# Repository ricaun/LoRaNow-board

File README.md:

# LoRaNow Board

LoRaNow Boards is a project with open source hardware using the Arduino (atmega328p) and LoRa Module (RFM95).

This boards were designed to work with [LoRaNow Library][3].

## LoRaNow v0

## LoRaNow v1

## License

<br />This work is licensed under a <a rel="license" href="http://creativecommons.org/licenses/by-nc-sa/4.0/">Creative Commons Attribution-NonCommercial-ShareAlike 4.0 International License</a>.

If you want to do commercial stuff with this project, please contact [ricaun][1] so we can organize an simple agreement.

## Blog

See news and other projects on my [blog][2] 

[1]: http://www.ricaun.com.br/#contact
[2]: http://www.loranow.com
[3]: https://github.com/ricaun/LoRaNow

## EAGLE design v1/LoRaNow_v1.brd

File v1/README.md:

# LoRaNow v1

LoRaNow Boards v1 is a PCB to help wiring between Atmega328p and RFM95 LoRa module to work with 2 AA batteries.

## Detailed Description

This board has:
* Footprint for Atmega328p
* Footprint for RFM95
* Footprint for P-Channel Mosfet to turn on/off the RFM95
* Classic I2C connector (VCC, GND, SCL, SDA)
* Footprint for Diodes (DIO0/DIO1/DIO2 to pin 2)
* Footprint for Ultra Low Power controller TPL5110 (Optional)

Look at the schematics for more informations.

Pins board connections.
```
  Arduino       RFM9x Module
  13 <--------> CLK
  12 <--------> MISO
  11 <--------> MOSI
  10 <--------> CS
  9  <--------> P-MOSFET
  2  <-DIODES-> DIO0/DIO1/DIO2
```

## Schematic

## Boards

## Bill Of Material

* Atmega328p (SMD)
* 8MHz cystal (SMD)
* RFM95 (check Frequency)
* Resistor 10k (603) (x2)
* Capacitor 1u (603)
* Capacitor 0.1u (603) (x5)
* P-Channel Mosfet (SOT23)
* 1N4148 (SOD123) (x3)
* Ultra Low Power controller TPL5110
* Resistor 124k (603)
* Battery holder (2xAA)
* Antenna 

## License

<br />This work is licensed under a <a rel="license" href="http://creativecommons.org/licenses/by-nc-sa/4.0/">Creative Commons Attribution-NonCommercial-ShareAlike 4.0 International License</a>.

If you want to do commercial stuff with this project, please contact [ricaun][1] so we can organize an simple agreement.

## Blog

See news and other projects on my [blog][2] 

[1]: http://www.ricaun.com.br/#contact
[2]: http://www.loranow.com

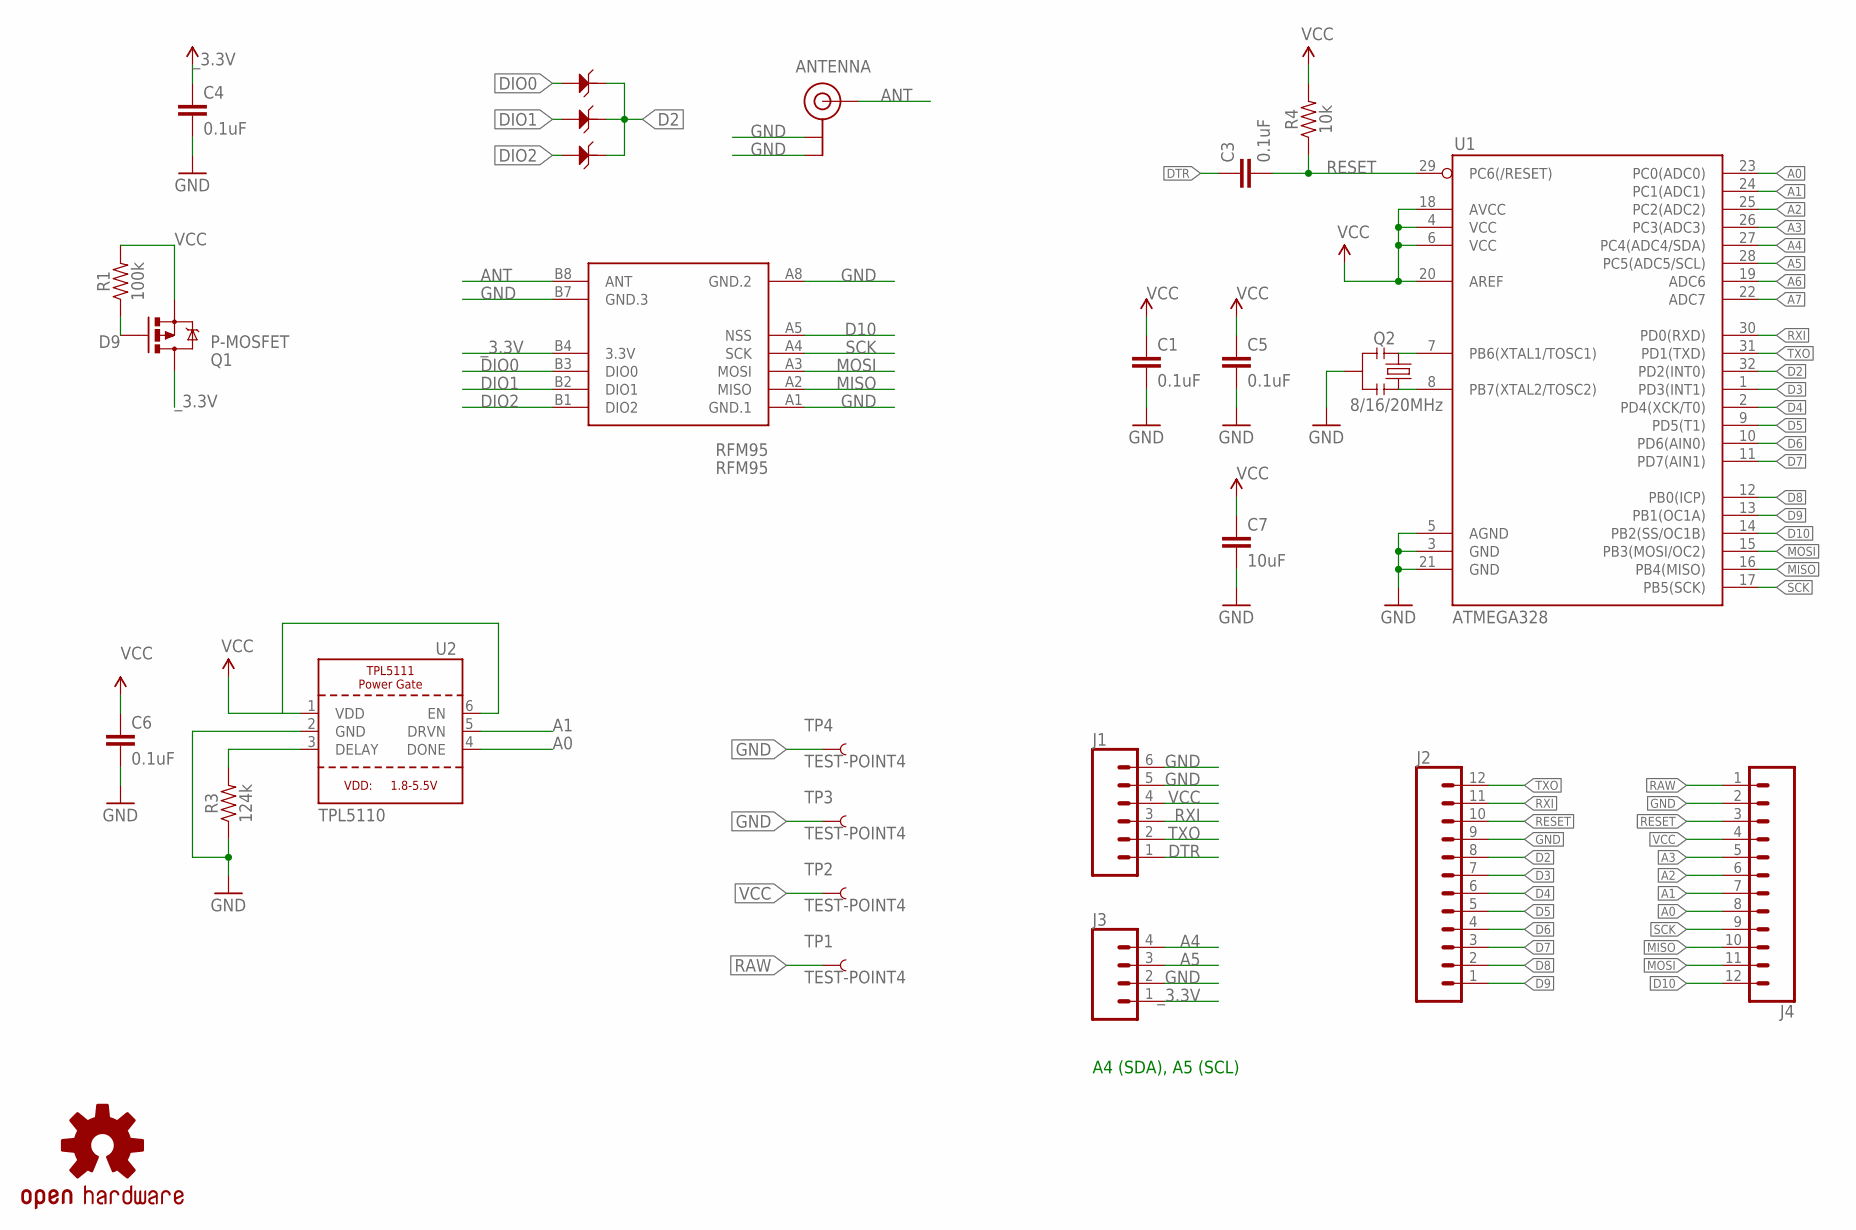
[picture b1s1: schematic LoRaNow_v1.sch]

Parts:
ANTENNA: U.FLU.FL_2A; U.FL_2A
C1, C3, C4, C5, C6: 0.1uF; 0603
C7: 10uF; 0603
D2, D3, D4: 1N4148; SOD123-2.7X1.6
J1: CONN_06NO_SILK_FEMALE_PTH; 1X06_NO_SILK
J2, J4: CONN_12NO_SILK; 1X12_NO_SILK
J3: CONN_041X04_NO_SILK; 1X04_NO_SILK
Q1: P-MOSFET; SOT23-3
Q2: 8/16/20MHz; RESONATOR-SMD-1:1
R1: 100k; 0603
R3: 124k; 0603
R4: 10k; 0603
RFM95: RFM95; WIRELESS-LORANOW-RFM95W#SMD#2
TP1, TP2, TP3, TP4: TEST-POINT4; PAD.02X.04
U1: ATMEGA328; TQFP32-08
U2: TPL5110; SOT23-6
U$3: OSHW-LOGOS; OSHW-LOGO-S

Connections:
A0: J4.8, U1.23 (PC0(ADC0)), U2.4 (DONE)
A1: J4.7, U1.24 (PC1(ADC1)), U2.5 (DRVN)
A2: J4.6, U1.25 (PC2(ADC2))
A3: J4.5, U1.26 (PC3(ADC3))
A4: J3.4, U1.27 (PC4(ADC4/SDA))
A5: J3.3, U1.28 (PC5(ADC5/SCL))
A6: U1.19 (ADC6)
A7: U1.22 (ADC7)
ANT: ANTENNA.FEED (SIGNAL), ANTENNA.FEED.B (SIGNAL), ANTENNA.FEED.P (SIGNAL), RFM95.B8 (ANT)
D2: D2.2, D3.2, D4.2, J2.8, U1.32 (PD2(INT0))
D3: J2.7, U1.1 (PD3(INT1))
D4: J2.6, U1.2 (PD4(XCK/T0))
D5: J2.5, U1.9 (PD5(T1))
D6: J2.4, U1.10 (PD6(AIN0))
D7: J2.3, U1.11 (PD7(AIN1))
D8: J2.2, U1.12 (PB0(ICP))
D9: J2.1, Q1.1 (G), R1.1, U1.13 (PB1(OC1A))
D10: J4.12, RFM95.A5 (NSS), U1.14 (PB2(SS/OC1B))
DELAY: R3.2, U2.3 (DELAY)
DIO0: D2.1, RFM95.B3 (DIO0)
DIO1: D3.1, RFM95.B2 (DIO1)
DIO2: D4.1, RFM95.B1 (DIO2)
DTR: C3.1, J1.1
GND: ANTENNA.1 (GND), ANTENNA.2 (GND), ANTENNA.3 (GND), ANTENNA.4 (GND), ANTENNA.5 (GND), ANTENNA.6 (GND), C1.2, C4.2, C5.2, C6.2, C7.2, J1.5, J1.6, J2.9, J3.2, J4.2, Q2.2, R3.1, RFM95.A1 (GND.1), RFM95.A8 (GND.2), RFM95.B7 (GND.3), TP3.P$1, TP4.P$1, U1.3 (GND), U1.5 (AGND), U1.21 (GND), U2.2 (GND)
MISO: J4.10, RFM95.A2 (MISO), U1.16 (PB4(MISO))
MOSI: J4.11, RFM95.A3 (MOSI), U1.15 (PB3(MOSI/OC2))
RAW: J4.1, TP1.P$1
RESET: C3.2, J2.10, J4.3, R4.1, U1.29 (PC6(/RESET))
RXI: J1.3, J2.11, U1.30 (PD0(RXD))
SCK: J4.9, RFM95.A4 (SCK), U1.17 (PB5(SCK))
TXO: J1.2, J2.12, U1.31 (PD1(TXD))
VCC: C1.1, C5.1, C6.1, C7.1, J1.4, J4.4, Q1.2 (S), R1.2, R4.2, TP2.P$1, U1.4 (VCC), U1.6 (VCC), U1.18 (AVCC), U1.20 (AREF), U2.1 (VDD), U2.6 (EN)
X1: Q2.1, U1.7 (PB6(XTAL1/TOSC1))
X2: Q2.3, U1.8 (PB7(XTAL2/TOSC2))
_3.3V: C4.1, J3.1, Q1.3 (D), RFM95.B4 (3.3V)

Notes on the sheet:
A4 (SDA), A5 (SCL)

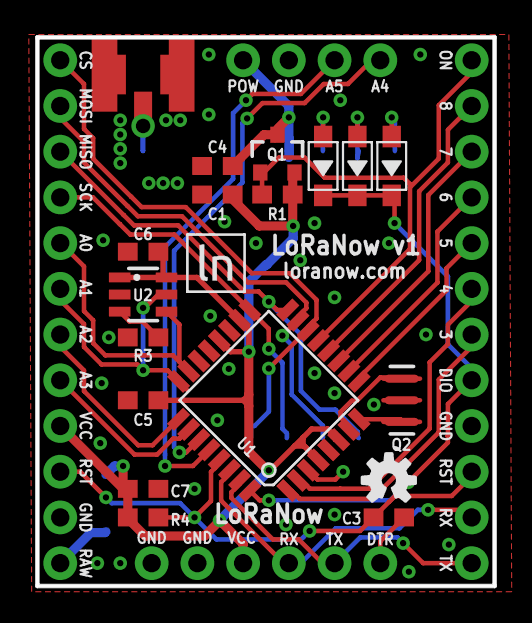
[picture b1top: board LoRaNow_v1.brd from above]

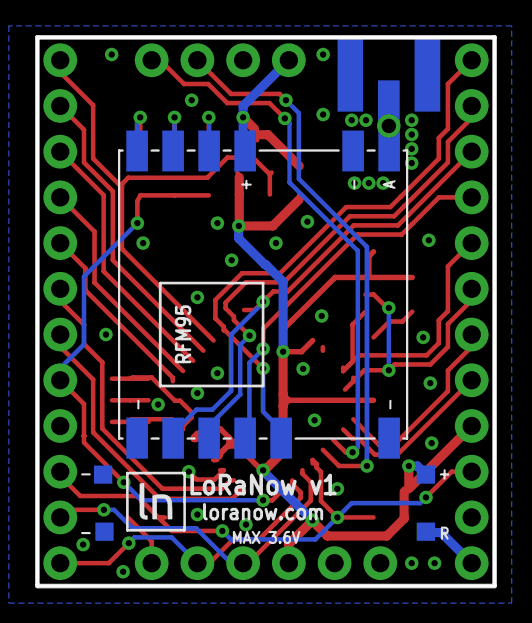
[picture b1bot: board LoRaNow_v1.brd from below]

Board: 2 copper layers, 25.4 x 30.5 mm, 29 parts (6 on the bottom side), 33 nets.

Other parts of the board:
U$7, U$8: LORANOW_SMALL_BOX

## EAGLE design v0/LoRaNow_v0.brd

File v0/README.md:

# LoRaNow v0

LoRaNow Boards v0 is a PCB to help wiring between Arduino Mini and RFM95 LoRa module to work with 2 AA batteries.

## Detailed Description

This board has:
* Footprint for Arduino Pro Mini
* Footprint for RFM95
* Footprint for P-Channel Mosfet to turn on/off the RFM95
* Classic I2C connector (VCC, GND, SCL, SDA)
* Jumper to DIO1/DIO2/RST for RFM95
* Jumper to VCC the P-Channel Mosfet

Look at the schematics for more informations.

Pins board connections.
```
  Arduino       RFM9x Module
  13 <--------> CLK
  12 <--------> MISO
  11 <--------> MOSI
  10 <--------> CS
  9  <--DRST--> RST
  8  <--------> P-MOSFET
  7  <--DIO2--> DIO2
  6  <--DIO1--> DIO1
  2  <--------> DIO0
```

## Schematic

## Boards

## Bill Of Material

* Arduino Pro Mini (8MHz)
* RFM95 (check Frequency)
* Capacitor 0.1u (603) (Optional)
* P-Channel Mosfet (SOT23) (Optional) 
* Resistor 10k (603) (Optional)
* Battery holder (2xAA)
* Antenna

## License

<br />This work is licensed under a <a rel="license" href="http://creativecommons.org/licenses/by-nc-sa/4.0/">Creative Commons Attribution-NonCommercial-ShareAlike 4.0 International License</a>.

If you want to do commercial stuff with this project, please contact [ricaun][1] so we can organize an simple agreement.

## Blog

See news and other projects on my [blog][2] 

[1]: http://www.ricaun.com.br/#contact
[2]: http://www.loranow.com

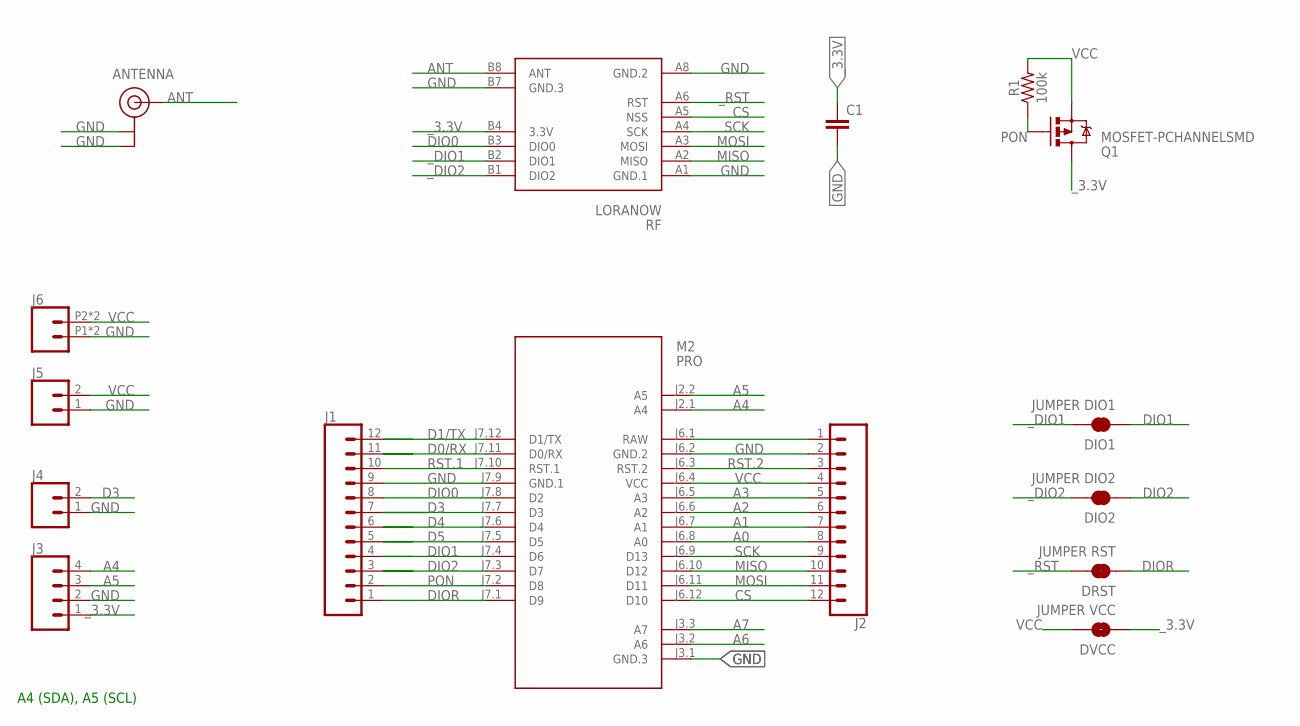
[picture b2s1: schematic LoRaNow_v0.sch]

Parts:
ANTENNA: U.FLU.FL2; U.FL_2
C1: C-EUC0603K; C0603K
DIO1: JUMPER DIO1; SMT-JUMPER_2_NC_TRACE_NO-SILK
DIO2: JUMPER DIO2; SMT-JUMPER_2_NC_TRACE_NO-SILK
DRST: JUMPER RST; SMT-JUMPER_2_NC_TRACE_NO-SILK
DVCC: JUMPER VCC; SMT-JUMPER_2_NO_NO-SILK
J1, J2: CONN_12NO_SILK; 1X12_NO_SILK
J3: CONN_041X04_NO_SILK; 1X04_NO_SILK
J4, J5: CONN_021X02_NO_SILK; 1X02_NO_SILK
J6: CONN_02SMALL_POKEHOME; 1X02_POKEHOME
M2: PRO; ARDUINO-PRO-MINI#NP#2
Q1: MOSFET-PCHANNELSMD; SOT23-3
R1: 100k; 0603
RF: LORANOW; WIRELESS-LORA-RFM95W#SMD#2

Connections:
A0: J2.8, M2.J6.8 (A0)
A1: J2.7, M2.J6.7 (A1)
A2: J2.6, M2.J6.6 (A2)
A3: J2.5, M2.J6.5 (A3)
A4: J3.4, M2.J2.1 (A4)
A5: J3.3, M2.J2.2 (A5)
A6: M2.J3.2 (A6)
A7: M2.J3.3 (A7)
ANT: ANTENNA.FEED (SIGNAL), ANTENNA.FEED.P (SIGNAL), RF.B8 (ANT)
CS: J2.12, M2.J6.12 (D10), RF.A5 (NSS)
D0/RX: J1.11, M2.J7.11 (D0/RX)
D1/TX: J1.12, M2.J7.12 (D1/TX)
D3: J1.7, J4.2, M2.J7.7 (D3)
D4: J1.6, M2.J7.6 (D4)
D5: J1.5, M2.J7.5 (D5)
DIO0: J1.8, M2.J7.8 (D2), RF.B3 (DIO0)
DIO1: DIO1.1, J1.4, M2.J7.4 (D6)
DIO2: DIO2.1, J1.3, M2.J7.3 (D7)
DIOR: DRST.1, J1.1, M2.J7.1 (D9)
GND: ANTENNA.1 (GND), ANTENNA.2 (GND), ANTENNA.3 (GND), ANTENNA.4 (GND), ANTENNA.5 (GND), ANTENNA.6 (GND), C1.2, J1.9, J2.2, J3.2, J4.1, J5.1, J6.P1 (1), J6.P3 (1), M2.J3.1 (GND.3), M2.J6.2 (GND.2), M2.J7.9 (GND.1), RF.A1 (GND.1), RF.A8 (GND.2), RF.B7 (GND.3)
MISO: J2.10, M2.J6.10 (D12), RF.A2 (MISO)
MOSI: J2.11, M2.J6.11 (D11), RF.A3 (MOSI)
PON: J1.2, M2.J7.2 (D8), Q1.1 (G), R1.1
RAW: J2.1, M2.J6.1 (RAW)
RST.1: J1.10, M2.J7.10 (RST.1)
RST.2: J2.3, M2.J6.3 (RST.2)
SCK: J2.9, M2.J6.9 (D13), RF.A4 (SCK)
VCC: DVCC.2, J2.4, J5.2, J6.P2 (2), J6.P4 (2), M2.J6.4 (VCC), Q1.2 (S), R1.2
_3.3V: C1.1, DVCC.1, J3.1, Q1.3 (D), RF.B4 (3.3V)
_DIO1: DIO1.2, RF.B2 (DIO1)
_DIO2: DIO2.2, RF.B1 (DIO2)
_RST: DRST.2, RF.A6 (RST)

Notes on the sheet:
A4 (SDA), A5 (SCL)

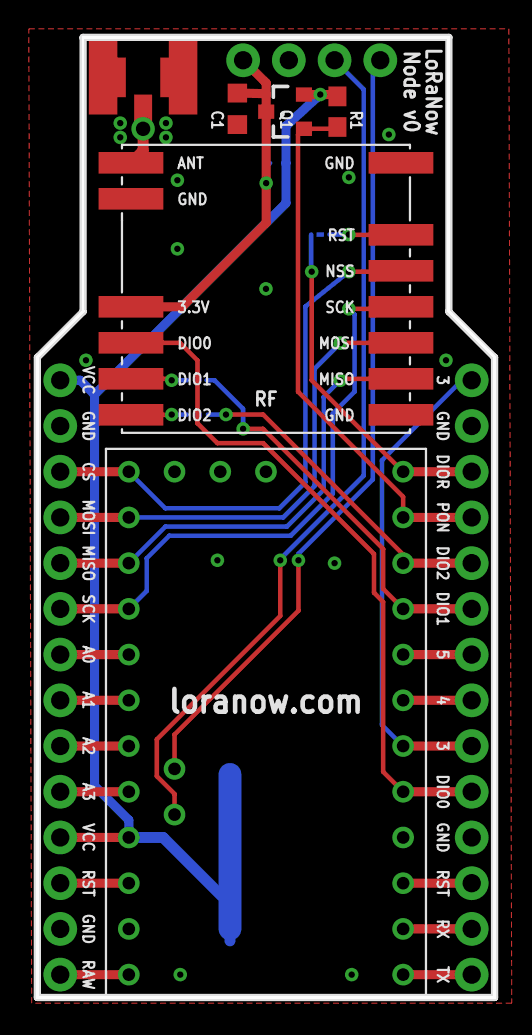
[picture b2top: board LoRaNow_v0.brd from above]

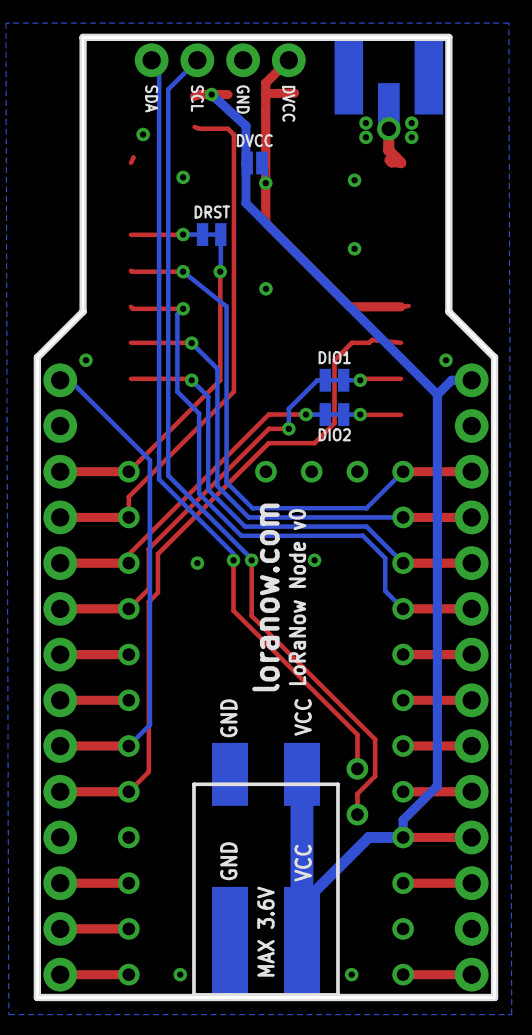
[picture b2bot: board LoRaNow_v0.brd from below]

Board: 2 copper layers, 25.4 x 53.3 mm, 16 parts (5 on the bottom side), 30 nets.

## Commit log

2019-05-10 First

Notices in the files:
parts and their libraries:
diy-modules: Released under the Creative Commons Attribution 4.0 International License: http://creativecommons.org/licenses/by/4.0
SparkFun-Connectors: Licensing: Creative Commons ShareAlike 4.0 International - https://creativecommons.org/licenses/by-sa/4.0
